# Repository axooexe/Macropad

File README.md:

<h1 align="center">⌨️ Custom 3x3 Macropad</h1>

A sleek, fully custom 3x3 macro pad built from the ground up for developers and creators. Designed with a custom PCB, a tailored 3D-printed enclosure, and snappy firmware mapped to a hyper-efficient creative workflow.

# Technical Specifications

࿔ Hardware:

Microcontroller: Adafruit KB2040 (RP2040) via USB-C

Keys: 8 MX-compatible mechanical switches (Hot-swappable)

Extra Controls: 1 Rotary encoder (for volume/scrolling)

࿔ Software & CAD Design:

PCB Design: KiCad

Enclosure Modeling: Blender, FreeCAD...

Firmware Development: VS Code

# ⌨️ Layer Shortcuts

Every key on this macropad fires a global system shortcut (`Super + Alt + Key`) to instantly launch or control workflows.

| Key / Control | Hardware Label | Triggered Shortcut | Target Action |
| :--- | :--- | :--- | :--- |
| **Key 1** | `S0` | <kbd>Super</kbd> + <kbd>Alt</kbd> + <kbd>0</kbd> | Launch GitHub (Browser) |
| **Key 2** | `S1` | <kbd>Super</kbd> + <kbd>Alt</kbd> + <kbd>1</kbd> | Launch Linux Terminal |
| **Key 3** | `S2` | <kbd>Super</kbd> + <kbd>Alt</kbd> + <kbd>2</kbd> | Launch Blender |
| **Key 4** | `S3` | <kbd>Super</kbd> + <kbd>Alt</kbd> + <kbd>3</kbd> | Launch Spotify |
| **Key 5** | `S4` | <kbd>Super</kbd> + <kbd>Alt</kbd> + <kbd>4</kbd> | Launch VS Code |
| **Key 6** | `S5` | <kbd>Super</kbd> + <kbd>Alt</kbd> + <kbd>5</kbd> | Launch Discord |
| **Key 7** | `S6` | <kbd>Super</kbd> + <kbd>Alt</kbd> + <kbd>6</kbd> | Launch Brave Browser |
| **Key 8** | `S7` | <kbd>Super</kbd> + <kbd>Alt</kbd> + <kbd>7</kbd> | Launch Arduino IDE |
| **Encoder Turn** | `E1` | *Hardware Volume* | Adjust System Volume (Up / Down) |
| **Encoder Click**| `E1` | <kbd>Super</kbd> + <kbd>Alt</kbd> + <kbd>9</kbd> | System Audio Mute / Unmute |

# 📁 Repository Map

├── 3D_Design

├── Firmware       

├── Hardware       

└── README.md

# Overview

### ★ PCB Schematics:

### ★ PCB Footprint:

### ★ PCB 3D Model:

### ★ 3D Printable Case:

Note: For the 3D case, this image is only an overview from FreeCAD, which caused its colors to disappear, but in the repository, there is a .mtl file that comes with the .obj file.

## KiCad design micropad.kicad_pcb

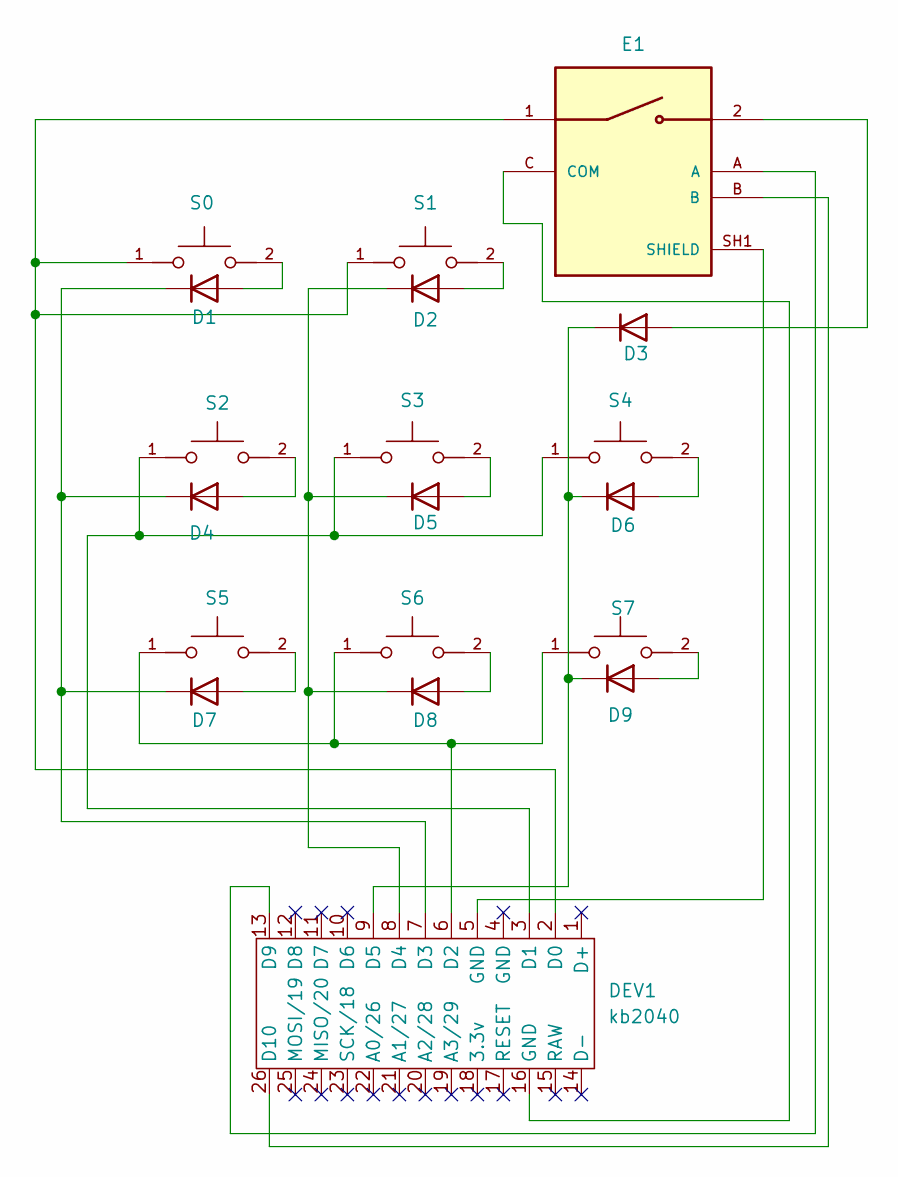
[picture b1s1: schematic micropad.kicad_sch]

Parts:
D1, D2, D3, D4, D5, D6, D7, D8, D9: 1N4148WT; D_SOD-523
DEV1: kb2040
E1: PEC11R-4220F-S0024; XDCR_PEC11R-4220F-S0024; PARTREV 11/23
S0, S1, S2, S3, S4, S5, S6, S7: MX1A-11NN; SW_MX1A-11NN

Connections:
unnamed: D1.2 (A), S0.2
unnamed: D1.1 (K), D4.1 (K), D7.1 (K), DEV1.7 (D3)
unnamed: D2.2 (A), S1.2
unnamed: D2.1 (K), D5.1 (K), D8.1 (K), DEV1.8 (D4)
unnamed: D3.2 (A), E1.2
unnamed: D3.1 (K), D6.1 (K), D9.1 (K), DEV1.9 (D5)
unnamed: D4.2 (A), S2.2
unnamed: D5.2 (A), S3.2
unnamed: D6.2 (A), S4.2
unnamed: D7.2 (A), S5.2
unnamed: D8.2 (A), S6.2
unnamed: D9.2 (A), S7.2
unnamed: DEV1.2 (D0), E1.1, S0.1, S1.1
unnamed: DEV1.3 (D1), S2.1, S3.1, S4.1
unnamed: DEV1.6 (D2), S5.1, S6.1, S7.1
unnamed: DEV1.13 (D9), E1.A
unnamed: DEV1.26 (D10), E1.B
unnamed: DEV1.5 (GND), E1.SH1 (SHIELD), E1.SH2 (SHIELD)
unnamed: DEV1.16 (GND), E1.C (COM)

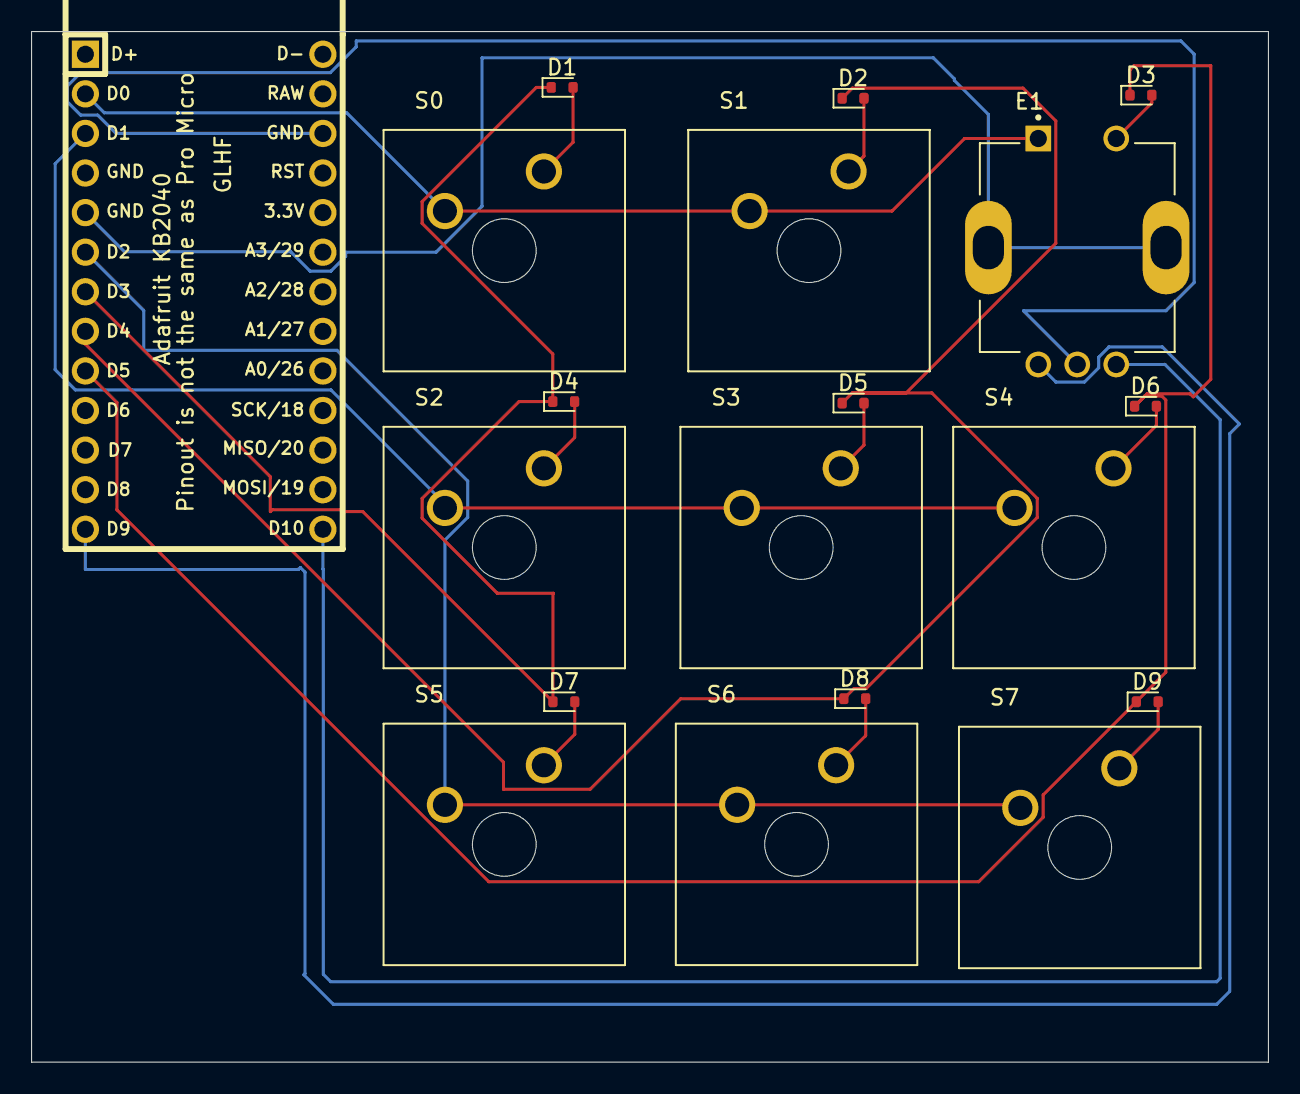
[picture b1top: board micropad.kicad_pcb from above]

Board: 2 copper layers, 79.4 x 66.1 mm, 19 parts (0 on the bottom side), 19 nets.

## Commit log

2026-06-07 pcb's schematics
2026-06-07 pcb's footprint
2026-06-07 pcb's code
2026-06-08 3D model (not finished)
2026-06-09 updated the 3d model
2026-06-10 Macropad's 3d case
2026-06-11 fixed bugs
    Removed encoder functionality and adjusted key handling.
2026-06-12 temporary
2026-06-12 we'll see
2026-06-12 added images
2026-06-12 chnaged
2026-06-12 readme
